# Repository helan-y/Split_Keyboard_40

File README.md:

# Split Keyboard 40%

## About
Custom split staggered ortholinear keyboard! Uses choc v2 switches with a rotary knob. 40% with custom layers.

## Idea
I don't particularly want carpal tunnel, and I've found that my typing habits are kind of terrible, so building a split keyboard would solve both of those issues. This is based off the ZSA voyager for layout, but a bit reduced for 40% layout. 

## PCB

## Schematic

## CAD

## Firmware
Firmware coded with QMK.

## BOM
- 40x choc v2 Low Profile Switches
- 2x LiPo 1800 mAh 
- 2x Seeeduino Xiao ESP32C3
- 2x JST PH 2 Pin Connector
- 40x 1N5819WS SOD-323 Diodes 
- 2x EC12 Rotary Encoder 12.5mm Half Cap
- 2x White Rotary Encoder Cap
- 40x Keycaps

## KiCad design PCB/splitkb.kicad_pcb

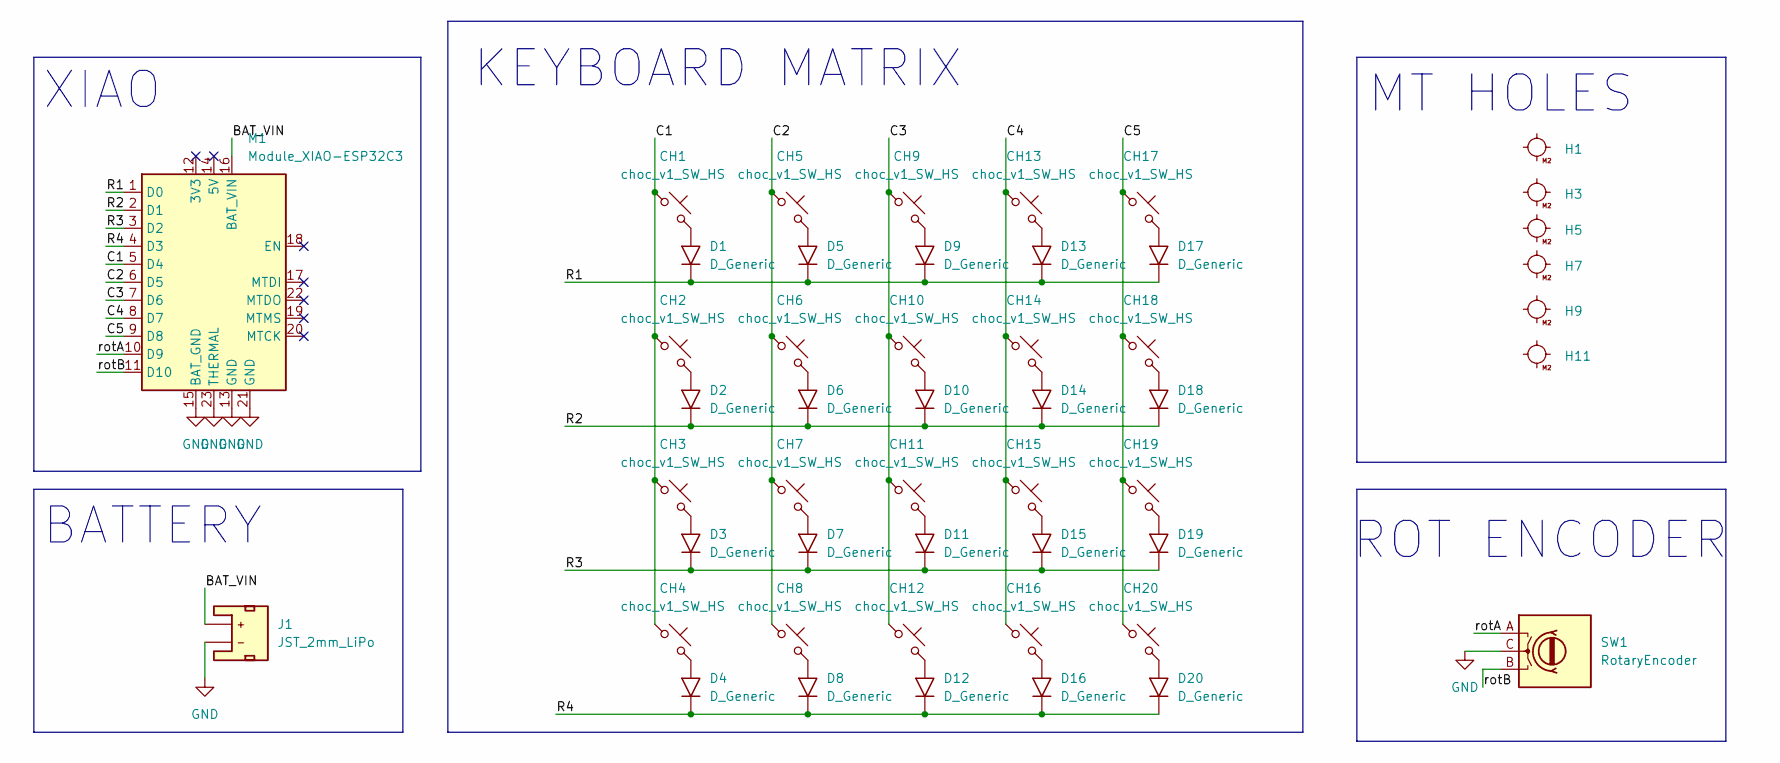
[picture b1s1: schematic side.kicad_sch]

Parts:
CH1, CH2, CH3, CH4, CH5, CH6, CH7, CH8, CH9, CH10, CH11, CH12, CH13, CH14, CH15, CH16, CH17, CH18, CH19, CH20: choc_v1_SW_HS; SW_choc_v2_1u
D1, D2, D3, D4, D5, D6, D7, D8, D9, D10, D11, D12, D13, D14, D15, D16, D17, D18, D19, D20: D_Generic; D_SOD-323_HandSoldering
H1, H3, H5, H7, H9, H11: MountingHole_M2
J1: JST_2mm_LiPo; JST_1x02_P2.0mm_Horizontal_SMD
M1: Module_XIAO-ESP32C3; SeeedStudio_XIAO_ESP32C3
SW1: RotaryEncoder; RotaryEncoder_Alps_EC12E_Vertical_H20mm

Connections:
/left/BAT_VIN: J1.2 (+), M1.16 (BAT_VIN)
/left/C1: CH1.1, CH2.1, CH3.1, CH4.1, M1.5 (D4)
/left/C2: CH5.1, CH6.1, CH7.1, CH8.1, M1.6 (D5)
/left/C3: CH9.1, CH10.1, CH11.1, CH12.1, M1.7 (D6)
/left/C4: CH13.1, CH14.1, CH15.1, CH16.1, M1.8 (D7)
/left/C5: CH17.1, CH18.1, CH19.1, CH20.1, M1.9 (D8)
/left/R1: D1.1 (K), D5.1 (K), D9.1 (K), D13.1 (K), D17.1 (K), M1.1 (D0)
/left/R2: D2.1 (K), D6.1 (K), D10.1 (K), D14.1 (K), D18.1 (K), M1.2 (D1)
/left/R3: D3.1 (K), D7.1 (K), D11.1 (K), D15.1 (K), D19.1 (K), M1.3 (D2)
/left/R4: D4.1 (K), D8.1 (K), D12.1 (K), D16.1 (K), D20.1 (K), M1.4 (D3)
/left/rotA: M1.10 (D9), SW1.A
/left/rotB: M1.11 (D10), SW1.B
GND: J1.1 (-), M1.13 (GND), M1.15 (BAT_GND), M1.21 (GND), M1.23 (THERMAL), SW1.C; also elsewhere on the board
unnamed: CH1.2, D1.2 (A)
unnamed: CH2.2, D2.2 (A)
unnamed: CH3.2, D3.2 (A)
unnamed: CH4.2, D4.2 (A)
unnamed: CH5.2, D5.2 (A)
unnamed: CH6.2, D6.2 (A)
unnamed: CH7.2, D7.2 (A)
unnamed: CH8.2, D8.2 (A)
unnamed: CH9.2, D9.2 (A)
unnamed: CH10.2, D10.2 (A)
unnamed: CH11.2, D11.2 (A)
unnamed: CH12.2, D12.2 (A)
unnamed: CH13.2, D13.2 (A)
unnamed: CH14.2, D14.2 (A)
unnamed: CH15.2, D15.2 (A)
unnamed: CH16.2, D16.2 (A)
unnamed: CH17.2, D17.2 (A)
unnamed: CH18.2, D18.2 (A)
unnamed: CH19.2, D19.2 (A)
unnamed: CH20.2, D20.2 (A)

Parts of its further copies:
CH21, CH22, CH23, CH24, CH25, CH26, CH27, CH28, CH29, CH30, CH31, CH32, CH33, CH34, CH35, CH36, CH37, CH38, CH39, CH40: choc_v1_SW_HS; SW_choc_v2_1u
D21, D22, D23, D24, D25, D26, D27, D28, D29, D30, D31, D32, D33, D34, D35, D36, D37, D38, D39, D40: D_Generic; D_SOD-323_HandSoldering
J2: JST_2mm_LiPo; JST_1x02_P2.0mm_Horizontal_SMD
M2: Module_XIAO-ESP32C3; SeeedStudio_XIAO_ESP32C3
SW2: RotaryEncoder; RotaryEncoder_Alps_EC12E_Vertical_H20mm

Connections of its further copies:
/right/BAT_VIN: J2.2 (+), M2.16 (BAT_VIN)
/right/C1: CH21.1, CH22.1, CH23.1, CH24.1, M2.5 (D4)
/right/C2: CH25.1, CH26.1, CH27.1, CH28.1, M2.6 (D5)
/right/C3: CH29.1, CH30.1, CH31.1, CH32.1, M2.7 (D6)
/right/C4: CH33.1, CH34.1, CH35.1, CH36.1, M2.8 (D7)
/right/C5: CH37.1, CH38.1, CH39.1, CH40.1, M2.9 (D8)
/right/R1: D21.1 (K), D25.1 (K), D29.1 (K), D33.1 (K), D37.1 (K), M2.1 (D0)
/right/R2: D22.1 (K), D26.1 (K), D30.1 (K), D34.1 (K), D38.1 (K), M2.2 (D1)
/right/R3: D23.1 (K), D27.1 (K), D31.1 (K), D35.1 (K), D39.1 (K), M2.3 (D2)
/right/R4: D24.1 (K), D28.1 (K), D32.1 (K), D36.1 (K), D40.1 (K), M2.4 (D3)
/right/rotA: M2.10 (D9), SW2.A
/right/rotB: M2.11 (D10), SW2.B
GND: J2.1 (-), M2.13 (GND), M2.15 (BAT_GND), M2.21 (GND), M2.23 (THERMAL), SW2.C; also elsewhere on the board
unnamed: CH21.2, D21.2 (A)
unnamed: CH22.2, D22.2 (A)
unnamed: CH23.2, D23.2 (A)
unnamed: CH24.2, D24.2 (A)
unnamed: CH25.2, D25.2 (A)
unnamed: CH26.2, D26.2 (A)
unnamed: CH27.2, D27.2 (A)
unnamed: CH28.2, D28.2 (A)
unnamed: CH29.2, D29.2 (A)
unnamed: CH30.2, D30.2 (A)
unnamed: CH31.2, D31.2 (A)
unnamed: CH32.2, D32.2 (A)
unnamed: CH33.2, D33.2 (A)
unnamed: CH34.2, D34.2 (A)
unnamed: CH35.2, D35.2 (A)
unnamed: CH36.2, D36.2 (A)
unnamed: CH37.2, D37.2 (A)
unnamed: CH38.2, D38.2 (A)
unnamed: CH39.2, D39.2 (A)
unnamed: CH40.2, D40.2 (A)

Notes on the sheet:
MT HOLES
XIAO
BATTERY
ROT ENCODER
KEYBOARD MATRIX

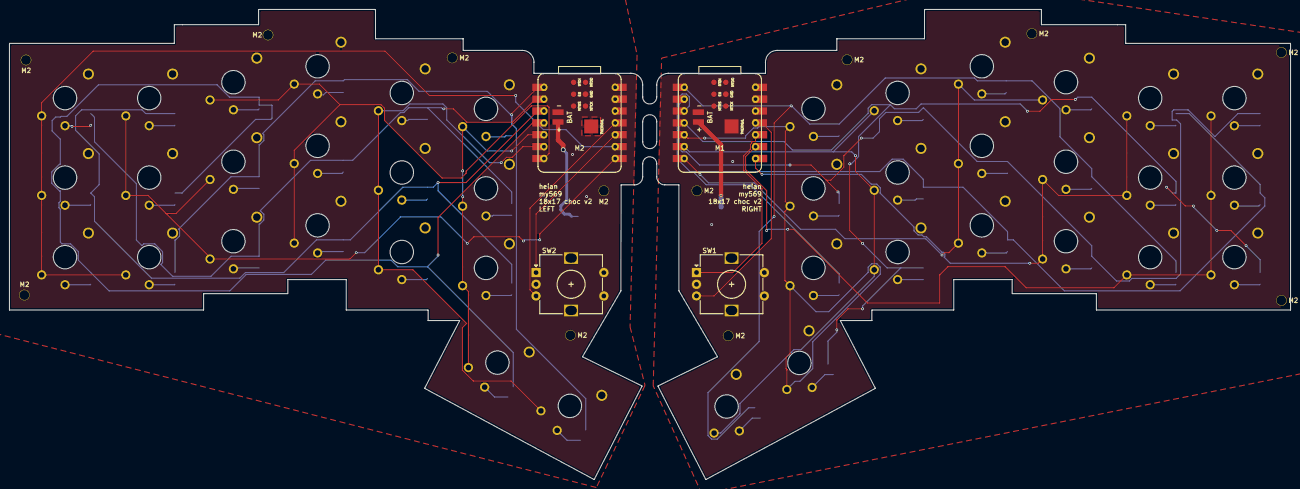
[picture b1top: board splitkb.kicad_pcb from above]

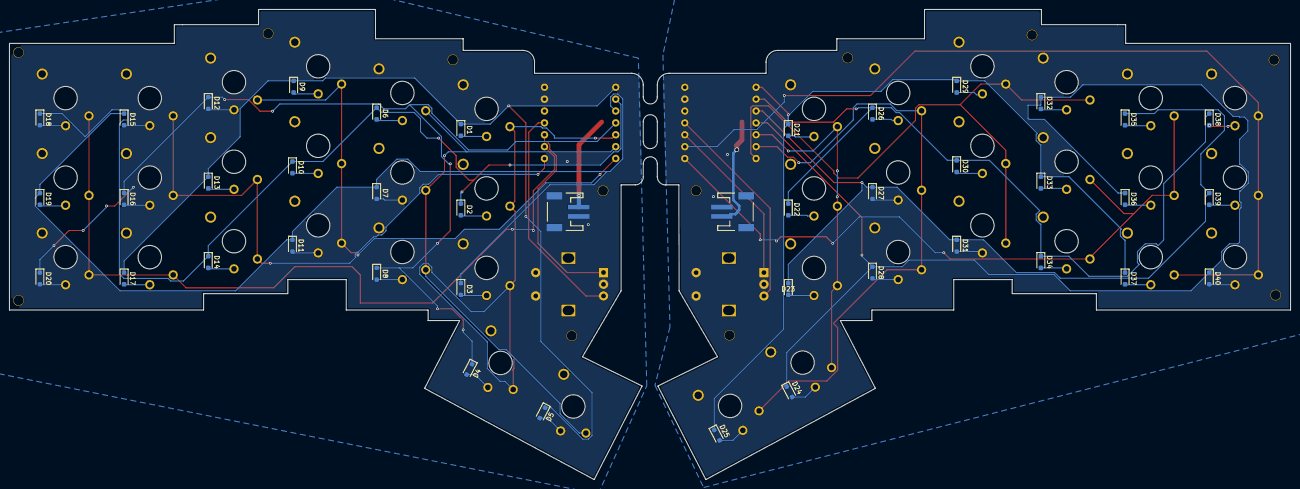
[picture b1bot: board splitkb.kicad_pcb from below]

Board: 2 copper layers, 273.9 x 100.5 mm, 98 parts (42 on the bottom side), 65 nets.

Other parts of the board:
H2, H4, H6, H8, H10, H12: MountingHole_M2

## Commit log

2026-06-24 modified pcb and production files
